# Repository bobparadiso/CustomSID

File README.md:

# CustomSID
Custom Specialty Input Device (SID) for Power Wheelchairs over the 9-pin connector on Omni and Q-Logic

Enables proportional driver controls of a power wheelchair. For more info:
https://bobparadiso.com/2018/10/09/custom-proportional-power-wheelchair-drive-controls/

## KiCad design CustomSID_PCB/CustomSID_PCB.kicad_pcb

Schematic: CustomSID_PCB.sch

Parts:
J1: Ethernet_Jack; RJ45_Amphenol_RJHSE538X
J2: DB9_Female; DSUB-9_Female_Horizontal_P2.77x2.84mm_EdgePinOffset7.70mm_H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
J3: AudioJack2_Ground_Switch; AudioJack
R1, R2: 1.8K; R_Axial_DIN0207_L6.3mm_D2.5mm_P10.16mm_Horizontal
R3: 470; R_Axial_DIN0207_L6.3mm_D2.5mm_P10.16mm_Horizontal
R4: 10k; R_Axial_DIN0207_L6.3mm_D2.5mm_P10.16mm_Horizontal
R5: 1k; R_Axial_DIN0207_L6.3mm_D2.5mm_P10.16mm_Horizontal
RV1: DISPLAY_SPEED; Potentiometer_Bourns_3386P_Vertical
RV2: DISPLAY_BRIGHTNESS; Potentiometer_Bourns_3386P_Vertical
U1: FeatherM0_Adalogger
U2: TSR 1-2450; Converter_DCDC_TRACO_TSR-1_THT
U3: AD5263; TSSOP-24_4.4x7.8mm_P0.65mm
U4: TL974; DIP-14_W7.62mm

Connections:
+3V3: RV1.1, RV2.1, U1.2, U3.10, U3.15
+5V: J1.2, U1.26, U2.3
+12V: J2.7, U2.1, U3.2, U3.5, U3.7, U3.23, U4.4 (V+)
/CS: U1.21, U3.13
/DIR: U3.22, U4.5 (+)
/DIR_BUF: R2.1, U4.6 (-), U4.7
/MODE: J2.6, U1.23
/MOSI: U1.12, U3.11
/REF: U3.6, U4.10 (+)
/REF_BUF: R3.1, U4.8, U4.9 (-)
/RES: R4.1, U1.22, U3.14
/SCK: U1.11, U3.12
/SPEED: U3.3, U4.3 (+)
/SPEED_BUF: R1.1, U4.1, U4.2 (-)
/TX: J1.3, U1.20
GND: J1.1, J1.SH, J2.8, J3.S, R4.2, RV1.3, RV2.3, U1.4, U2.2, U3.1, U3.4, U3.8, U3.9, U3.18, U3.24, U4.11 (V-)
unnamed: J2.1, R1.2
unnamed: J2.2, R2.2
unnamed: J2.3, R3.2
unnamed: J3.T, R5.1
unnamed: R5.2, U1.7
unnamed: RV1.2, U1.5
unnamed: RV2.2, U1.6

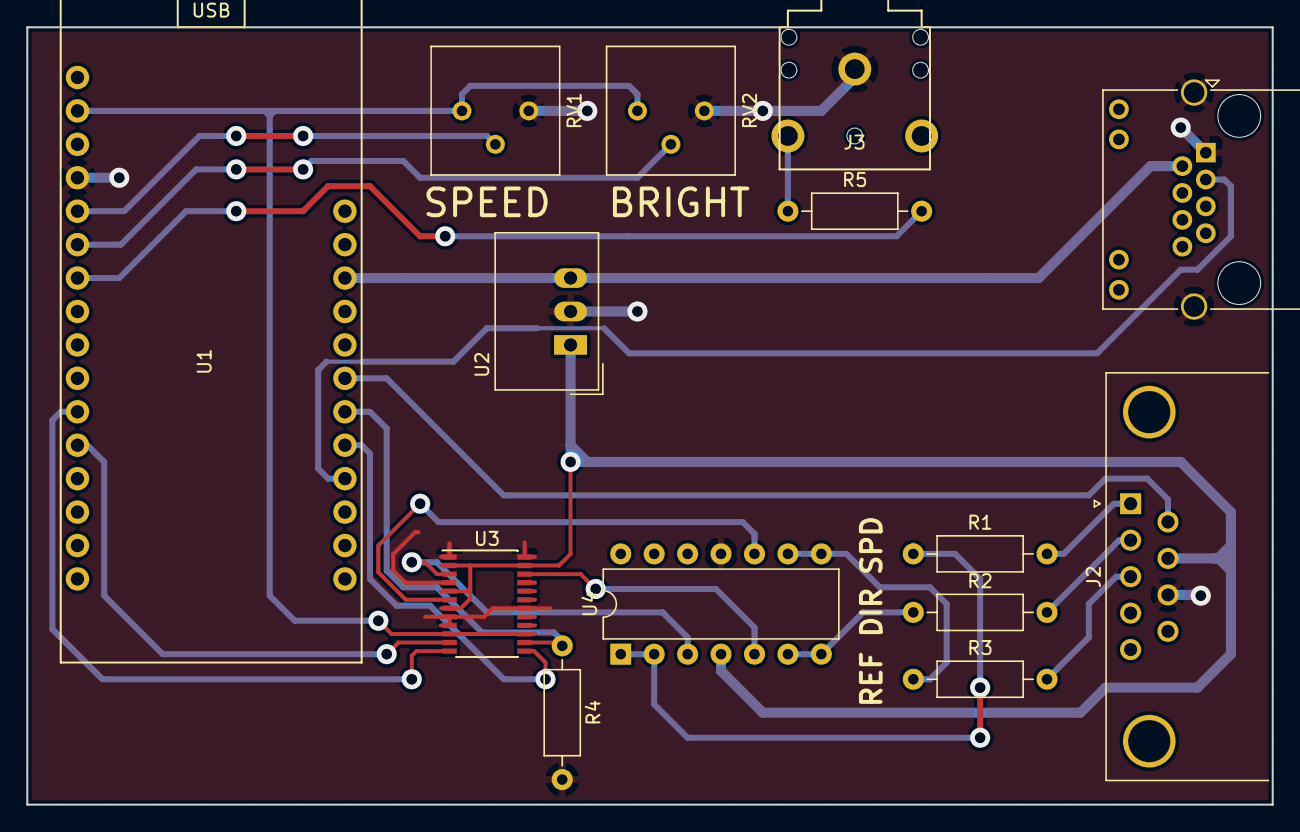
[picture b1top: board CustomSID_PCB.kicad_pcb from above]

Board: 2 copper layers, 94.6 x 59.1 mm, 14 parts (0 on the bottom side), 23 nets.

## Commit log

2022-03-05 Add files via upload
    -dump of source for all variations prototyped in 2018
